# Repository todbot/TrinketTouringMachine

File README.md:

# Trinket Touring Machine

Eurorack module based around Trinket M0

Initially started as an homage to Music Thing Modular's "Turing Machine" module, but as evolved into something more like an algorithmic melody generator.

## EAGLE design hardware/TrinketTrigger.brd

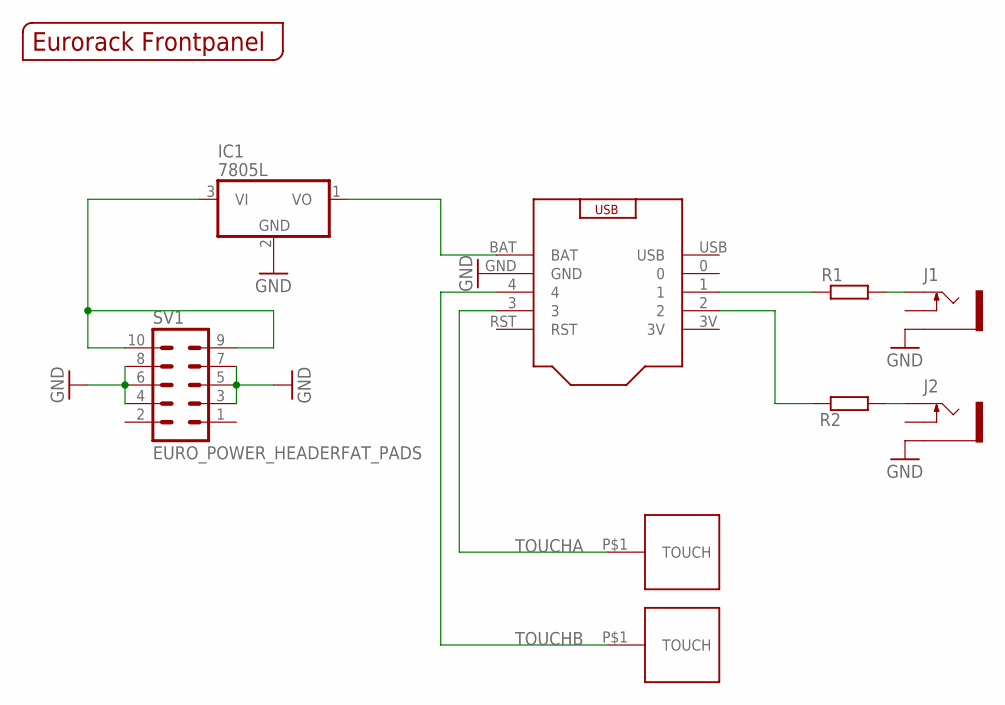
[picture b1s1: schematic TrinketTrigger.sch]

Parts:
IC1: 7805L; TO92
J1, J2: THONKICONNNEW; WQP-PJ301M-12_JACK
R1, R2: R-EU_0204/5; 0204/5
SV1: EURO_POWER_HEADERFAT_PADS; EURO_PWR_HEADER_FAT
U$1: EURORACK_PANEL6HP; EURORACK6HPPANEL
U$2: TRINKETM0NH; TRINKETMO_NOHOLES
U$3, U$4: TOUCHPADA

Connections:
GND: IC1.2 (GND), J1.P$3_SLEEVE (SLEEVE), J2.P$3_SLEEVE (SLEEVE), SV1.3, SV1.4, SV1.5, SV1.6, SV1.7, SV1.8, U$2.GND
unnamed: J1.P$1_TIP (TIP), R1.2
unnamed: J2.P$1_TIP (TIP), R2.2
unnamed: IC1.1 (VO), U$2.BAT
unnamed: IC1.3 (VI), SV1.9, SV1.10
unnamed: R1.1, U$2.1
unnamed: R2.1, U$2.2
TOUCHA: U$2.3, U$3.P$1
TOUCHB: U$2.4, U$4.P$1

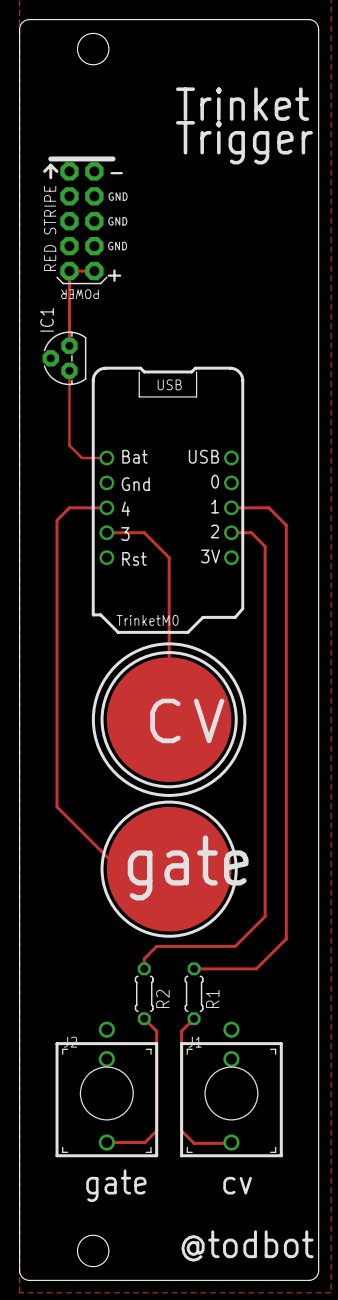
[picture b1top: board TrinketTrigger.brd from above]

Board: 2 copper layers, 30.5 x 128.5 mm, 10 parts (0 on the bottom side), 9 nets.

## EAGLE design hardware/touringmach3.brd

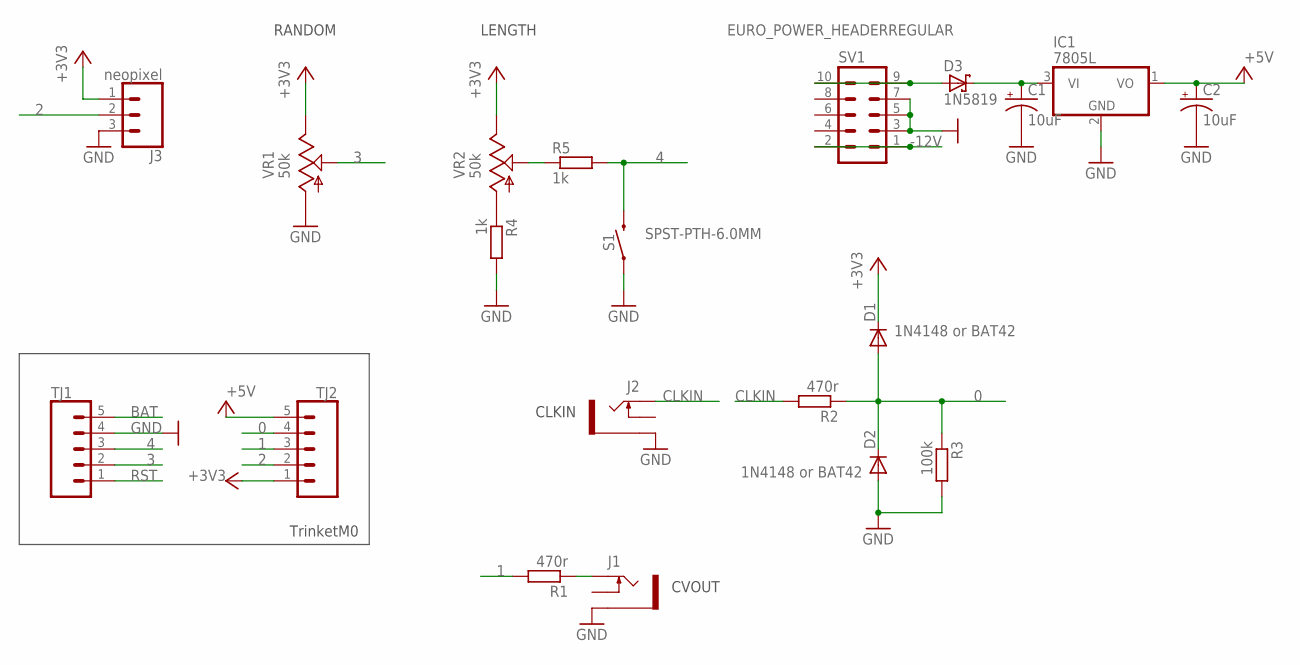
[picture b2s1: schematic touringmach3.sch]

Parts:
C1, C2: 10uF; E2,5-6
D1, D2: 1N4148 or BAT42; DO34-7
D3: 1N5819; DO41-7.6
IC1: 7805L; TO92
J1, J2: THONKICONNOLD; THONKICONN
J3: neopixel; 1X03
R1, R2: 470r; 7MM_RESISTOR
R3: 100k; 7MM_RESISTOR
R4, R5: 1k; 7MM_RESISTOR
S1: SPST-PTH-6.0MM; TACTILE_SWITCH_PTH_6.0MM
SV1: EURO_POWER_HEADERREGULAR; EURO_POWER_HEADER
TJ1, TJ2: CONN_05; 1X05
VR1, VR2: 50k; 9MM_SNAP-IN_POT

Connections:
0: D1.A, D2.C, R2.1, R3.1, TJ2.4
1: R1.2, TJ2.3
2: J3.2, TJ2.2
3: TJ1.2, VR1.2 (S)
4: R5.2, S1.3 (2), TJ1.3
+3V3: D1.C, J3.1, TJ2.1, VR1.3 (E), VR2.3 (E)
+5V: C2.+, IC1.1 (VO), TJ2.5
-12V: SV1.1, SV1.2
BAT: TJ1.5
CLKIN: J2.P$3_TIP (TIP), R2.2
GND: C1.-, C2.-, D2.A, IC1.2 (GND), J1.P$1_SLEEVE (SLEEVE), J2.P$1_SLEEVE (SLEEVE), J3.3, R3.2, R4.2, S1.1, SV1.3, SV1.5, SV1.7, TJ1.4, VR1.1 (A)
unnamed: J1.P$3_TIP (TIP), R1.1
unnamed: C1.+, D3.C, IC1.3 (VI)
unnamed: D3.A, SV1.9, SV1.10
unnamed: R4.1, VR2.1 (A)
unnamed: R5.1, VR2.2 (S)
RST: TJ1.1

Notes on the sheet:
TrinketM0
CVOUT
CLKIN
RANDOM
LENGTH

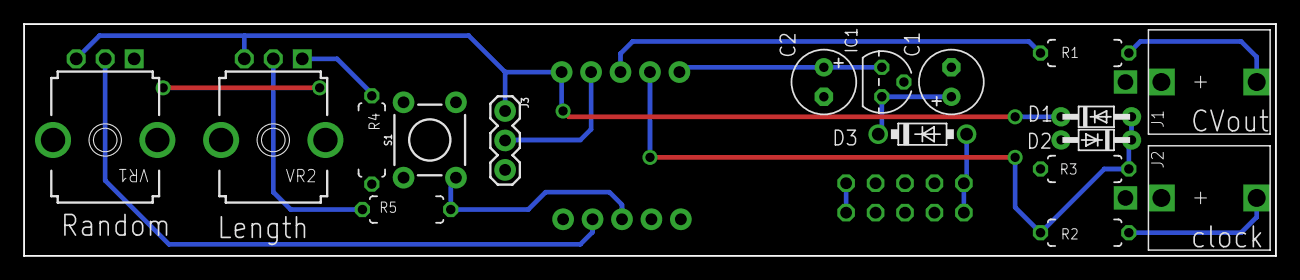
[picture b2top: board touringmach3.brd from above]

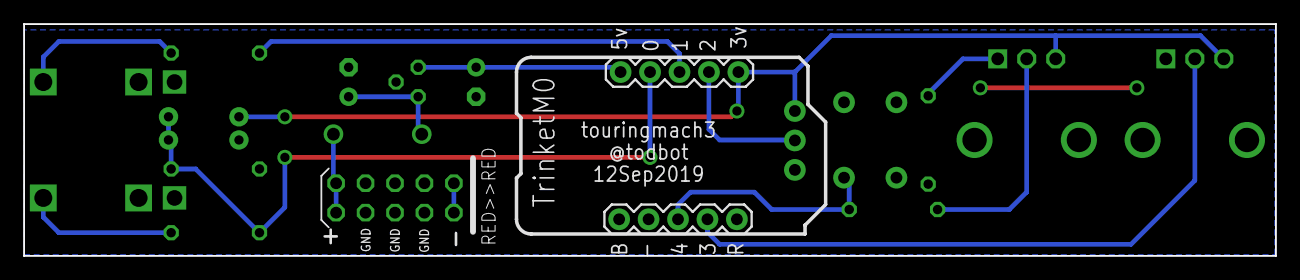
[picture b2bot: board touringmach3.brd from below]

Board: 2 copper layers, 108.0 x 20.0 mm, 20 parts (3 on the bottom side), 15 nets.

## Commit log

2019-09-12 awesome
2019-09-12 fix formatting
2019-09-15 more progress
2019-09-15 first cut at clock detection
2019-09-15 more clock detection work
2019-09-16 visual rep of int/ext clk
2019-09-17 fix latest sketch
2020-05-09 added TrinketTrigger
2020-08-21 added circuitpython veresion of some ideas
2020-08-21 added image
2020-08-21 unchecked in changes to old code
2020-08-21 put debug after output to improve output lag

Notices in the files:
parts and their libraries:
SparkFun-Connectors: Licensing: Creative Commons ShareAlike 4.0 International - https://creativecommons.org/licenses/by-sa/4.0
